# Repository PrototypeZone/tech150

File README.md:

# tech150

[TECH 150 Course Outline](https://humber.ca/transferoptions/course-outlines/outline.html?code=TECH%20150)

Welcome to TECH 150 - Please attend your labs with your parts kit and your [lab manual](https://www.bkstr.com/humberitstore/product/laboratory-exercises-for-electronic-devices-272165-1). Bookstore will possibly be restocked 2025-05-23.

[Parts Crib Signout](https://vladporcila.github.io/#partscribSignout)

[Semilog graphing example](https://www.mathnstuff.com/math/spoken/here/2class/340/gif/lgf3.gif)

2025 May-June Lab Schedule (Tentative)

|Week|A         |B         |Topics/Assignment                                           | Due %                                   |
|----|----------|----------|------------------------------------------------------------|-----------------------------------------|
|1   |2025-05-07|2025-05-08|Exp. 1 Part 1, Part 2: Introduction to Semiconductors [xy mode](https://www.youtube.com/watch?v=aIy5UbxMNug)|Show lab01 measurements                  |
|2   |2025-05-14|2025-05-15|[Exp. 2 (rectification and clipping during lab) Part 1, Part 2, Part 3: Diodes and Applications](https://www.youtube.com/watch?v=afHMWO7I1to) [We have MultiSim on myApps](https://www.youtube.com/watch?v=boqO6ccq-40)|Lab01 paper copy, Show lab02 measurements|
|    |2025-05-19|2025-05-19|Monday Public Holiday (Victoria Day) - College Closed       |                                         |
|3   |2025-05-21|2025-05-22|Exp. 3 Part 1: Special Purpose Diodes Steps 1-9 Conclusion/Questions: Part 1: 1,2,3|Lab02 paper copy, Show lab03 Table 3-2|
|4   |          |2025-05-29|Exp. 8 Part 1 Steps 1-10 step 11 IDSS (IDS with VGS shorted), Part 3: Field-Effect Transistors (FETs) (Part 1 Step 2 should read Keep VGG at 0V and slowly increase VDD (to about 1.4V) until VDS is 1.0V and Part3 Rs use 220Ohm, Rd use 3.3kOhm)     |Lab03 paper copy, Show lab04 measurements|
|    |2025-06-04|          |Exp. 8 Part 1 Steps 1-10 step 11 IDSS (IDS with VGS shorted), Part 3: Field-Effect Transistors (FETs) (Part 1 Step 2 should read Keep VGG at 0V and slowly increase VDD (to about 1.4V) until VDS is 1.0V and Part3 Rs use 220Ohm, Rd use 3.3kOhm)     |Lab03 paper copy, Show lab04 measurements|
|    |          |          |                                                            |                                         |
|5   |          |2025-06-05|Exp. 9 Part 1 (Step 4 use Rs=560 Ohm instead of 620 Ohm), Part 2: FET Amplifiers and Switching Circuits|Lab04 paper copy, Show lab05 measurements|
|    |          |          |                                                            |                                         |
|    |          |          |Reminder  that parts signed out from the parts crib are to be returned the same day|                  |
|6   |2025-06-11|          |Exp. 9 Part 1 (Step 4 use Rs=560 Ohm instead of 620 Ohm)           |Submit Exp. 8 Part 1 and Part 3 paper copy|
|    |          |          |Show the completed Table 9-2 prior to leaving the lab.      |                                         |
|    |          |          |For next week:                                              |                                         |
|    |          |          |-Each student is to build Figure 9-2 (without the JFET before the lab)|                               |
|    |          |          |-Regarding submitting part 1, please make sure that you are submitting on paper you have rights to|   |
|    |          |          |                                                            |                                         |
|    |          |2025-06-12|Exp. 9 Part 3: FET Amplifiers (Use R2=560Ohm, R3=200kOhm, R4=470kOhm)  |Lab05 paper copy, Show lab06 measurements|
|    |          |          |-Regarding recording measurements for part 3, please make sure that you are writing/submitting Tables 9-6,9-7,9-8,9-9, Step 6 What effect if any? Q1 and Q2 on paper you have rights to||
|    |          |          |                                                            |                                         |
|7   |2025-06-18|          |Individual Lab Overall Evaluation Figure 9-2 built without the JFET prior to the lab (5%)|Exp.9 Part 1 paper copy, labtest1|
|    |          |2025-06-19|Individual Lab Overall Evaluation Figure 9-2 built without the JFET prior to the lab (5%)|Exp.9 Part 3 paper copy, labtest1|
|    |          |          |                                                            |                                         |
|    |          |          |                                                            |                                         |
|    |2025-06-25|2025-06-26|*Reading Week, No Class Scheduled*                          |                                         |

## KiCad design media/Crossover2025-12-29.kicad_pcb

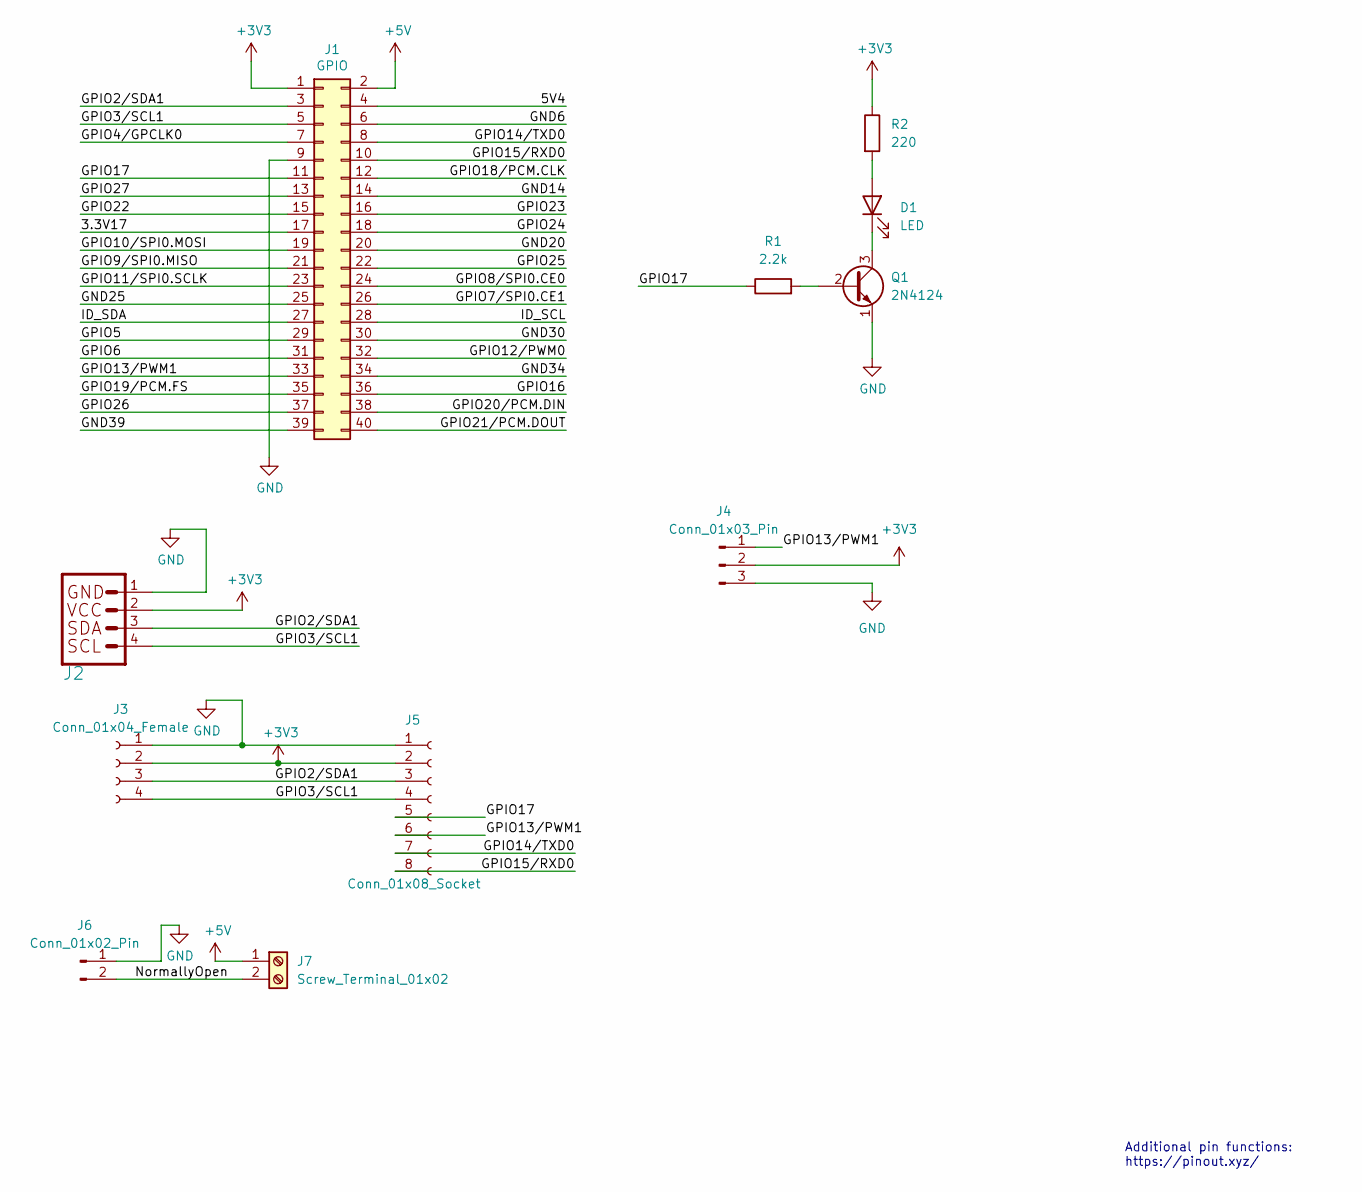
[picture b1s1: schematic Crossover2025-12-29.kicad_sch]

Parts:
D1: LED; LED_D5.0mm_Horizontal_O1.27mm_Z3.0mm
J1: GPIO; PinSocket_2x20_P2.54mm_Vertical
J2: Qwiic Right Angle; PinSocket_1x04_P2.00mm_Horizontal
J3: Conn_01x04_Female; PinSocket_1x04_P2.54mm_Horizontal
J4: Conn_01x03_Pin; PinHeader_1x03_P2.54mm_Horizontal
J5: Conn_01x08_Socket; PinSocket_1x08_P2.54mm_Horizontal
J6: Conn_01x02_Pin; JST_PH_S2B-PH-K_1x02_P2.00mm_Horizontal
J7: Screw_Terminal_01x02; TerminalBlock_Phoenix_MPT-0,5-2-2.54_1x02_P2.54mm_Horizontal
Q1: 2N4124; TO-92_Inline_Wide
R1: 2.2k; R_Axial_DIN0207_L6.3mm_D2.5mm_P15.24mm_Horizontal
R2: 220; R_Axial_DIN0207_L6.3mm_D2.5mm_P15.24mm_Horizontal

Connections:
+3V3: J1.1, J2.2, J3.2, J4.2, J5.2, R2.1
+5V: J1.2, J7.1
/3.3V17: J1.17
/5V4: J1.4
/GND6: J1.6
/GND14: J1.14
/GND20: J1.20
/GND25: J1.25
/GND30: J1.30
/GND34: J1.34
/GND39: J1.39
/GPIO2/SDA1: J1.3, J2.3, J3.3, J5.3
/GPIO3/SCL1: J1.5, J2.4, J3.4, J5.4
/GPIO4/GPCLK0: J1.7
/GPIO5: J1.29
/GPIO6: J1.31
/GPIO7/SPI0.CE1: J1.26
/GPIO8/SPI0.CE0: J1.24
/GPIO9/SPI0.MISO: J1.21
/GPIO10/SPI0.MOSI: J1.19
/GPIO11/SPI0.SCLK: J1.23
/GPIO12/PWM0: J1.32
/GPIO13/PWM1: J1.33, J4.1, J5.6
/GPIO14/TXD0: J1.8, J5.7
/GPIO15/RXD0: J1.10, J5.8
/GPIO16: J1.36
/GPIO17: J1.11, J5.5, R1.1
/GPIO18/PCM.CLK: J1.12
/GPIO19/PCM.FS: J1.35
/GPIO20/PCM.DIN: J1.38
/GPIO21/PCM.DOUT: J1.40
/GPIO22: J1.15
/GPIO23: J1.16
/GPIO24: J1.18
/GPIO25: J1.22
/GPIO26: J1.37
/GPIO27: J1.13
/ID_SCL: J1.28
/ID_SDA: J1.27
/NormallyOpen: J6.2, J7.2
GND: J1.9, J2.1, J3.1, J4.3, J5.1, J6.1, Q1.1 (E)
unnamed: D1.2 (A), R2.2
unnamed: D1.1 (K), Q1.3 (C)
unnamed: Q1.2 (B), R1.2

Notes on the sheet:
Additional pin functions: https://pinout.xyz/

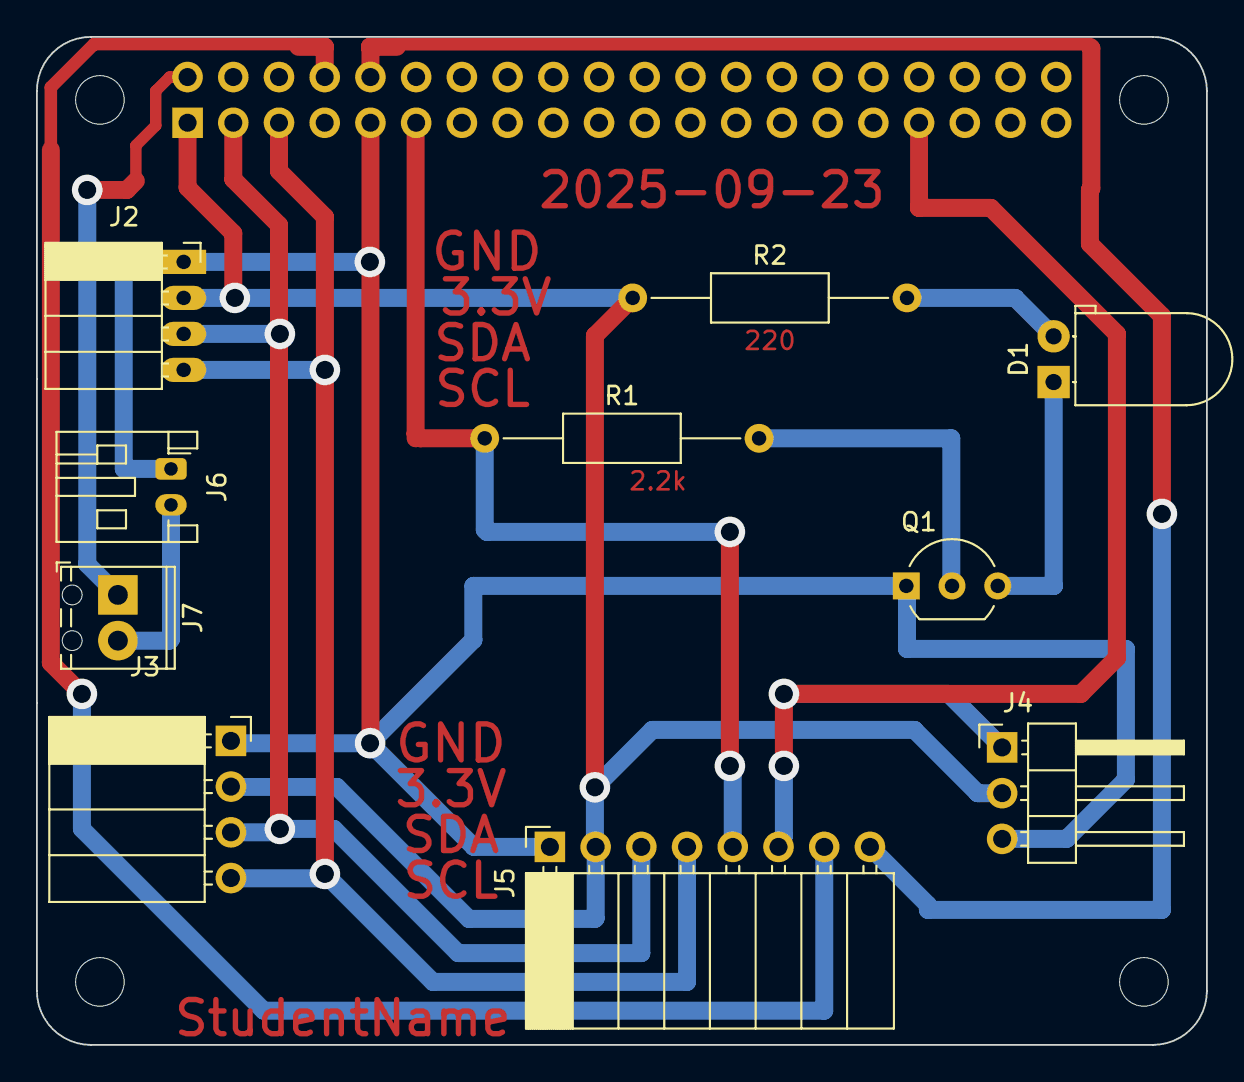
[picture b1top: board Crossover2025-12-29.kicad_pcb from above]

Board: 2 copper layers, 65.0 x 56.0 mm, 15 parts (1 on the bottom side), 13 nets.

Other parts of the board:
MH1, MH2, MH3, MH4: MountingHole_2.7mm_M2.5

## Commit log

2025-12-29 Create crossover.md for KiCad simulation guide
    Added a new markdown file for crossover simulation instructions using KiCad.
2025-12-29 Refactor introduction for audio crossover simulation
2025-12-29 Update instructions to open SCH file instead of PCB
2025-12-29 Update crossover.md to mention spice plugin
2025-12-29 Add references to external crossover resources
2025-12-29 Update crossover.md with suggested reading
    Added suggested reading for audio crossover simulation.
2026-01-02 Update crossover.md with new steps
2026-01-03 Revise KiCad setup and simulation instructions
    Updated instructions for using KiCad with new file structure and added simulation steps.
2026-01-03 Fix formatting of checklist item in crossover.md
2026-01-03 Fix markdown formatting for plot image
